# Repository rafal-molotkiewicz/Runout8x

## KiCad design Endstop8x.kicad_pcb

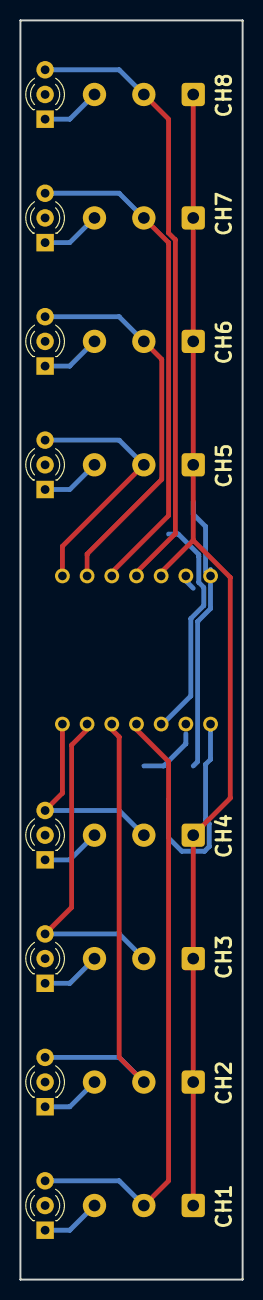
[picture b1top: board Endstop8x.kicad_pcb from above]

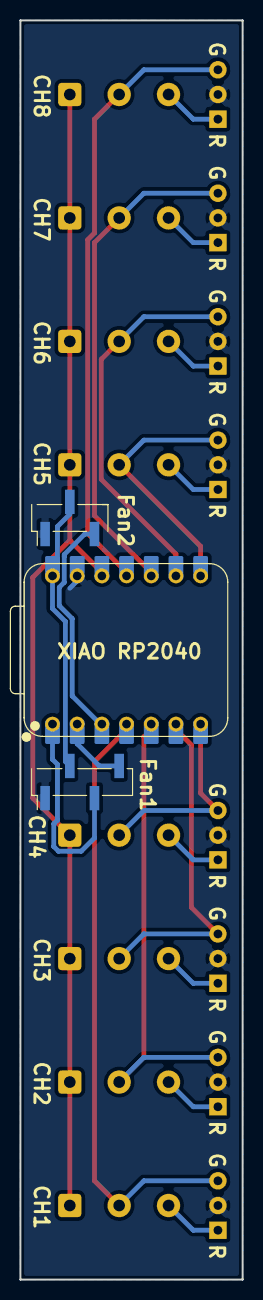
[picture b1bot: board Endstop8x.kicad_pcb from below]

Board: 2 copper layers, 22.9 x 129.5 mm, 19 parts (3 on the bottom side), 22 nets.

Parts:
D1, D2, D3, D4, D5, D6, D7, D8: LED_Dual_AKA; LED_D3.0mm-3
M1: Fan_Tacho; PinHeader_1x03_P2.54mm_Vertical_SMD_Pin1Left
M2: Fan_Tacho_PWM; PinHeader_1x04_P2.54mm_Vertical_SMD_Pin1Left
Omron D2F-01F1, Omron D2F-01F2, Omron D2F-01F3, Omron D2F-01F4, Omron D2F-01F5, Omron D2F-01F6, Omron D2F-01F7, Omron D2F-01F8: Omron_D2F-01F
U1: XIAO-RP2040-SMD; XIAO-RP2040-DIP

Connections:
/Channel1/GND: D1.2 (K), D2.2 (K), D3.2 (K), D4.2 (K), D5.2 (K), D6.2 (K), D7.2 (K), D8.2 (K), M1.1 (-), M2.1 (-), U1.13 (GND)
/Channel1/PWR: Omron D2F-01F1.1 (COM), Omron D2F-01F2.1 (COM), Omron D2F-01F3.1 (COM), Omron D2F-01F4.1 (COM), Omron D2F-01F5.1 (COM), Omron D2F-01F6.1 (COM), Omron D2F-01F7.1 (COM), Omron D2F-01F8.1 (COM), U1.12 (3V3_OUT)
/Channel1/SIG: D1.3 (A2), Omron D2F-01F1.2 (NO), U1.4 (D3)
/Channel2/SIG: D2.3 (A2), Omron D2F-01F2.2 (NO), U1.5 (D4)
/Channel3/SIG: D3.3 (A2), Omron D2F-01F3.2 (NO), U1.6 (D5)
/Channel4/SIG: D4.3 (A2), Omron D2F-01F4.2 (NO), U1.7 (D6)
/Channel5/SIG: D5.3 (A2), Omron D2F-01F5.2 (NO), U1.8 (D7)
/Channel6/SIG: D6.3 (A2), Omron D2F-01F6.2 (NO), U1.9 (D8)
/Channel7/SIG: D7.3 (A2), Omron D2F-01F7.2 (NO), U1.10 (D9)
/Channel8/SIG: D8.3 (A2), Omron D2F-01F8.2 (NO), U1.11 (D10)
unnamed: D1.1 (A1), Omron D2F-01F1.3 (NC)
unnamed: D2.1 (A1), Omron D2F-01F2.3 (NC)
unnamed: D3.1 (A1), Omron D2F-01F3.3 (NC)
unnamed: D4.1 (A1), Omron D2F-01F4.3 (NC)
unnamed: D5.1 (A1), Omron D2F-01F5.3 (NC)
unnamed: D6.1 (A1), Omron D2F-01F6.3 (NC)
unnamed: D7.1 (A1), Omron D2F-01F7.3 (NC)
unnamed: D8.1 (A1), Omron D2F-01F8.3 (NC)
unnamed: M1.2 (+), M2.2 (+), U1.14 (VBUS)
unnamed: M1.3 (Tacho), U1.3 (D2)
unnamed: M2.4 (PWM), U1.2 (D1)
unnamed: M2.3 (Tacho), U1.1 (D0)
